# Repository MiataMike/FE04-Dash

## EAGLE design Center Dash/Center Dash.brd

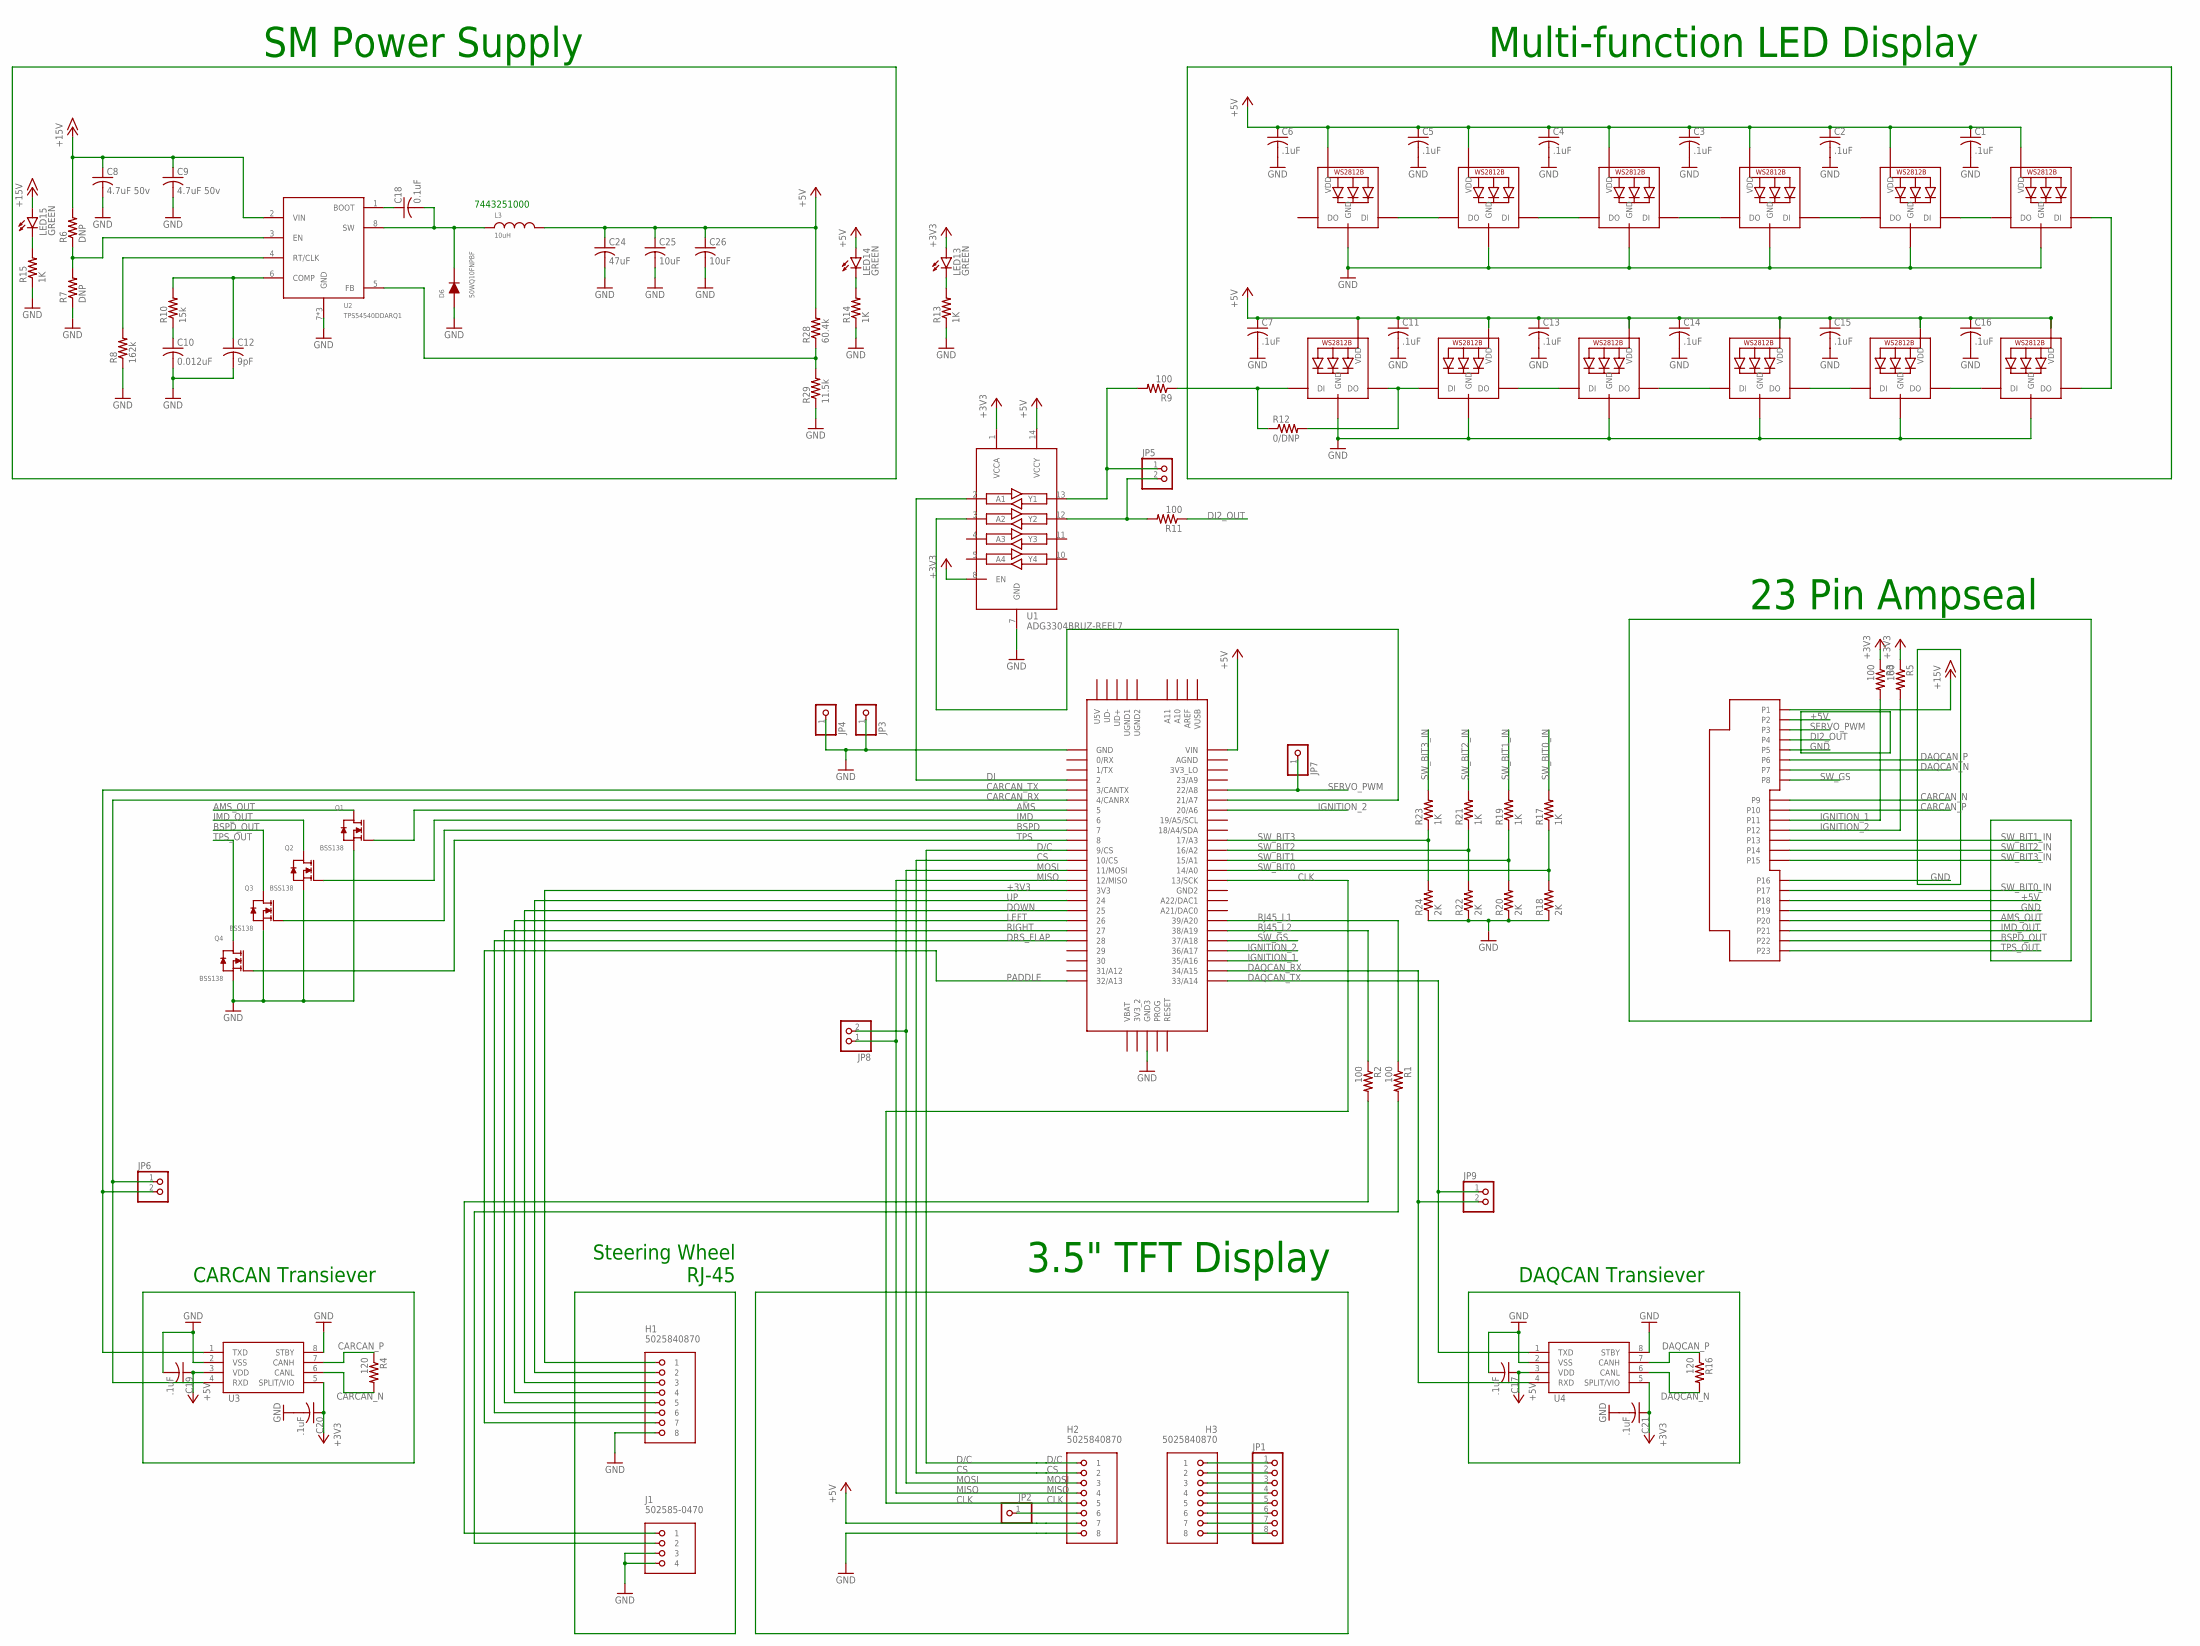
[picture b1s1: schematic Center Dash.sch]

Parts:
C1, C2, C3, C4, C5, C6, C7, C11, C13, C14, C15, C16: .1uF; C0603K; PARTNO GRM188R61A106KE69D
C8, C9: 4.7uF 50v; C1206; PARTNO GRM31CR71H475KA12L
C10: 0.012uF; C0603K; PARTNO GRM188R71H123KA01D
C12: 9pF; C0603K; PARTNO GRM1885C1H9R0DA01D
C17, C19, C20, C21: .1uF; C0805
C18: 0.1uF; C0603K; PARTNO GRM188R71E104KA01D
C24: 47uF; C1206; PARTNO GRM31CR61A476ME15L
C25, C26: 10uF; C0603K; PARTNO GRM188R61A106KE69D
D6: 50WQ10FNPBF; DPAK; PARTNO VS-50WQ10FNPBF
H1, H2, H3: 5025840870; MOLEX-CLIKMATE-8-VERTICAL-HEADER
J1: 502585-0470; MOLEX-CLIKMATE-4-R/A
JP1: PINHD-1X8; 1X08
JP2, JP3, JP4, JP7: PINHD-1X1; 1X01
JP5, JP6, JP8, JP9: PINHD-1X2; 1X02
L3: 10uH; WURTH-744325XXXX; PARTNO 7443251000
LED1, LED2, LED3, LED4, LED5, LED6, LED7, LED8, LED9, LED10, LED11, LED12: WS2812B5050; WS2812B
LED13, LED14, LED15: GREEN; CHIP-LED0805; PARTNO 598-8170-107F
Q1, Q2, Q3, Q4: BSS138
R1, R2, R3, R5, R9, R11: 100; R0805
R4, R16: 120; R0805
R6, R7: DNP; R0603; PARTNO *
R8: 162k; R0603; PARTNO ERJ-3EKF1623V
R10: 15k; R0603; PARTNO ERJ-3EKF1502V
R12: 0/DNP; R0805
R13, R14, R15, R17, R19, R21, R23: 1K; R0805; PARTNO ERJ-6ENF1001V
R18, R20, R22, R24: 2K; R0805; PARTNO ERJ-6ENF1001V
R28: 60.4k; R0603; PARTNO ERJ-3EKF6042V
R29: 11.5k; R0603; PARTNO ERJ-3EKF1152V
U1: ADG3304BRUZ-REEL7; ADG3304
U2: TPS54540DDARQ1; TPS54540; PARTNO TPS54540DDAR
U3, U4: MCP256X-SOIC; SOIC8-N_MC
U$1: TE-776200-1
U$2: TEENSY_3.5/3.6

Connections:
5VREG_EN: R6.1, R7.2, U2.3 (EN)
+3V3: C20.1, C21.1, H1.1, LED13.A, R3.1, R5.1, U1.1 (VCCA), U1.8 (EN), U3.5 (SPLIT/VIO), U4.5 (SPLIT/VIO), U$2.3V3
+5V: C1.1, C2.1, C3.1, C4.1, C5.1, C6.1, C7.1, C11.1, C13.1, C14.1, C15.1, C16.1, C17.1, C19.1, C24.1, C25.1, C26.1, H2.7, L3.P$2, LED1.1-VDD (VDD), LED2.1-VDD (VDD), LED3.1-VDD (VDD), LED4.1-VDD (VDD), LED5.1-VDD (VDD), LED6.1-VDD (VDD), LED7.1-VDD (VDD), LED8.1-VDD (VDD), LED9.1-VDD (VDD), LED10.1-VDD (VDD), LED11.1-VDD (VDD), LED12.1-VDD (VDD), LED14.A, R28.2, U1.14 (VCCY), U3.3 (VDD), U4.3 (VDD), U$1.P$2 (P2), U$1.P$18 (P18), U$2.VIN
+15V: C8.1, C9.1, LED15.A, R6.2, U2.2 (VIN), U$1.P$1 (P1)
AMS: Q1.G, U$2.5
AMS_OUT: Q1.D, U$1.P$20 (P20)
BOOT_5V: C18.1, U2.1 (BOOT)
BSPD: Q3.G, U$2.7
BSPD_OUT: Q3.D, U$1.P$22 (P22)
CARCAN_N: R4.2, U3.6 (CANL), U$1.P$9 (P9)
CARCAN_P: R4.1, U3.7 (CANH), U$1.P$10 (P10)
CARCAN_RX: JP6.1, U3.4 (RXD), U$2.4/CANRX
CARCAN_TX: JP6.2, U3.1 (TXD), U$2.3/CANTX
CLK: H2.5, U$2.13/SCK
COMP_5V: C12.1, R10.2, U2.6 (COMP)
CS: H2.2, U$2.10/CS
D/C: H2.1, U$2.9/CS
DAQCAN_N: R16.2, U4.6 (CANL), U$1.P$7 (P7)
DAQCAN_P: R16.1, U4.7 (CANH), U$1.P$6 (P6)
DAQCAN_RX: JP9.2, U4.4 (RXD), U$2.34/A15
DAQCAN_TX: JP9.1, U4.1 (TXD), U$2.33/A14
DI: U1.2 (A1), U$2.2
DI2_MORE: JP5.2, R11.2, U1.12 (Y2)
DI2_OUT: R11.1, U$1.P$4 (P4)
DI_MORE: U1.3 (A2), U$2.21/A7
DOWN: H1.3, U$2.25
DRS_FLAP: H1.6, U$2.28
FB_5V: R28.1, R29.2, U2.5 (FB)
GND: C1.2, C2.2, C3.2, C4.2, C5.2, C6.2, C7.2, C8.2, C9.2, C10.2, C11.2, C12.2, C13.2, C14.2, C15.2, C16.2, C17.2, C19.2, C20.2, C21.2, C24.2, C25.2, C26.2, D6.1 (ANODE), D6.3 (ANODE), H1.8, H2.8, J1.3, J1.4, JP3.1, JP4.1, LED1.3-GND (GND), LED2.3-GND (GND), LED3.3-GND (GND), LED4.3-GND (GND), LED5.3-GND (GND), LED6.3-GND (GND), LED7.3-GND (GND), LED8.3-GND (GND), LED9.3-GND (GND), LED10.3-GND (GND), LED11.3-GND (GND), LED12.3-GND (GND), Q1.S, Q2.S, Q3.S, Q4.S, R7.1, R8.1, R13.1, R14.1, R15.1, R18.1, R20.1, R22.1, R24.1, R29.1, U1.7 (GND), U2.7 (GND), U2.PAD (GND), U2.PAD1 (GND), U3.2 (VSS), U3.8 (STBY), U4.2 (VSS), U4.8 (STBY), U$1.P$5 (P5), U$1.P$16 (P16), U$1.P$19 (P19), U$2.GND, U$2.GND3
IGNITION_1: R3.2, U$1.P$11 (P11), U$2.35/A16
IGNITION_2: R5.2, U$1.P$12 (P12), U$2.20/A6, U$2.36/A17
IMD: Q2.G, U$2.6
IMD_OUT: Q2.D, U$1.P$21 (P21)
LEFT: H1.4, U$2.26
MISO: H2.4, JP8.1, U$2.12/MISO
MOSI: H2.3, JP8.2, U$2.11/MOSI
unnamed: LED1.2-DOUT (DO), LED2.4-DIN (DI), R12.2
unnamed: H3.1, JP1.1
unnamed: LED2.2-DOUT (DO), LED3.4-DIN (DI)
unnamed: LED3.2-DOUT (DO), LED4.4-DIN (DI)
unnamed: LED4.2-DOUT (DO), LED5.4-DIN (DI)
unnamed: LED5.2-DOUT (DO), LED6.4-DIN (DI)
unnamed: LED6.2-DOUT (DO), LED7.4-DIN (DI)
unnamed: LED1.4-DIN (DI), R9.1, R12.1
unnamed: H3.2, JP1.2
unnamed: H3.3, JP1.3
unnamed: H3.4, JP1.4
unnamed: H3.5, JP1.5
unnamed: H3.6, JP1.6
unnamed: H3.7, JP1.7
unnamed: LED14.C, R14.2
unnamed: JP5.1, R9.2, U1.13 (Y1)
unnamed: LED15.C, R15.2
unnamed: H3.8, JP1.8
unnamed: H2.6, JP2.1
unnamed: C10.1, R10.1
unnamed: J1.1, R2.2
unnamed: J1.2, R1.2
unnamed: LED7.2-DOUT (DO), LED8.4-DIN (DI)
unnamed: LED8.2-DOUT (DO), LED9.4-DIN (DI)
unnamed: LED9.2-DOUT (DO), LED10.4-DIN (DI)
unnamed: LED10.2-DOUT (DO), LED11.4-DIN (DI)
unnamed: LED11.2-DOUT (DO), LED12.4-DIN (DI)
unnamed: LED13.C, R13.2
PADDLE: H1.7, U$2.32/A13
RIGHT: H1.5, U$2.27
RJ45_L1: R1.1, U$2.39/A20
RJ45_L2: R2.1, U$2.38/A19
RT_5V: R8.2, U2.4 (RT/CLK)
SERVO_PWM: JP7.1, U$1.P$3 (P3), U$2.22/A8
SW_5V: C18.2, D6.2 (CATHODE), L3.P$1, U2.8 (SW)
SW_BIT0: R17.1, R18.2, U$2.14/A0
SW_BIT0_IN: R17.2, U$1.P$17 (P17)
SW_BIT1: R19.1, R20.2, U$2.15/A1
SW_BIT1_IN: R19.2, U$1.P$13 (P13)
SW_BIT2: R21.1, R22.2, U$2.16/A2
SW_BIT2_IN: R21.2, U$1.P$14 (P14)
SW_BIT3: R23.1, R24.2, U$2.17/A3
SW_BIT3_IN: R23.2, U$1.P$15 (P15)
SW_GS: U$1.P$8 (P8), U$2.37/A18
TPS: Q4.G, U$2.8
TPS_OUT: Q4.D, U$1.P$23 (P23)
UP: H1.2, U$2.24

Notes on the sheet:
7443251000
Steering Wheel RJ-45
Multi-function LED Display
3.5" TFT Display
23 Pin Ampseal
SM Power Supply
CARCAN Transiever
DAQCAN Transiever

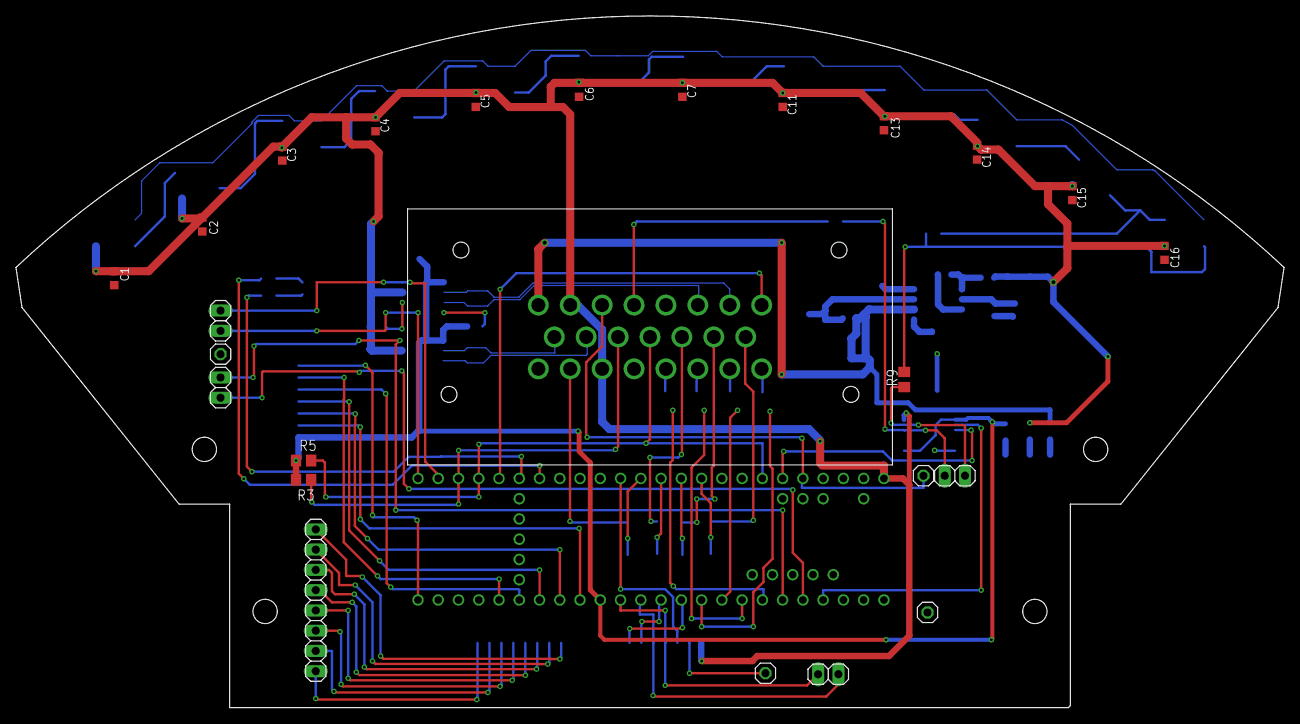
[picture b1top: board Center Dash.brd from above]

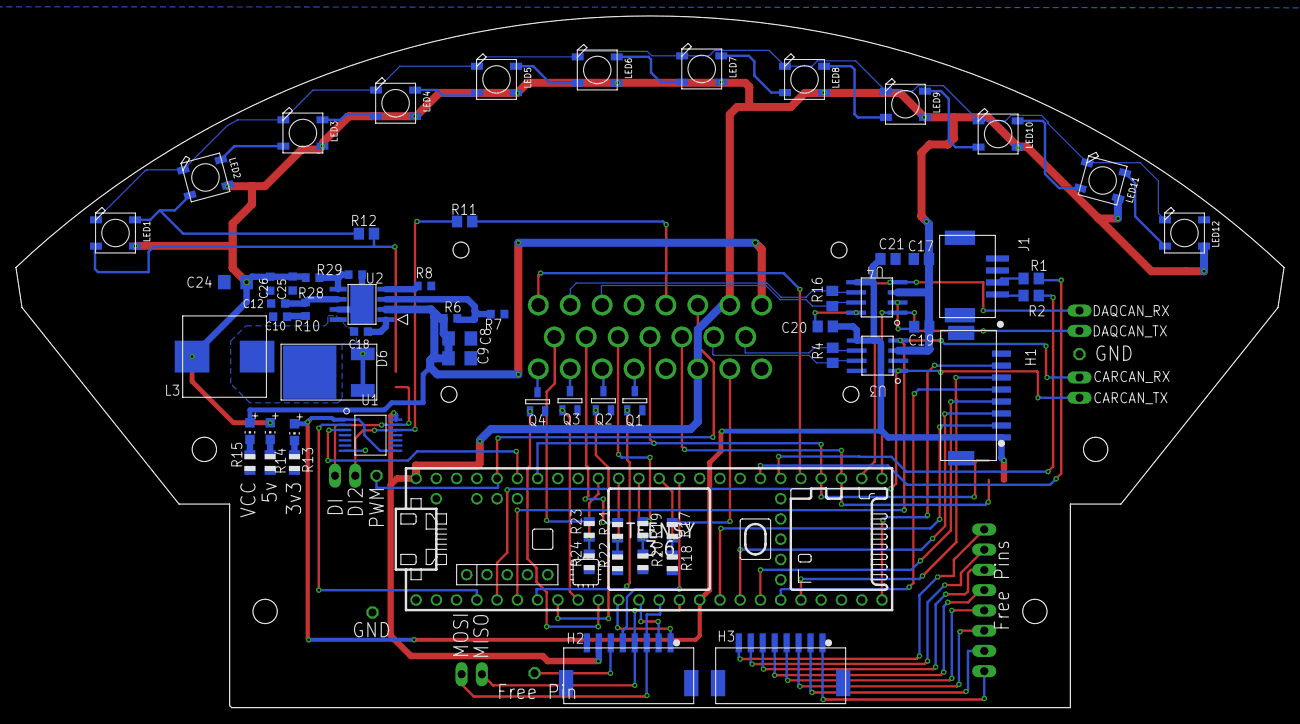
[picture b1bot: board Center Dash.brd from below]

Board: 2 copper layers, 159.0 x 86.7 mm, 90 parts (65 on the bottom side), 83 nets.

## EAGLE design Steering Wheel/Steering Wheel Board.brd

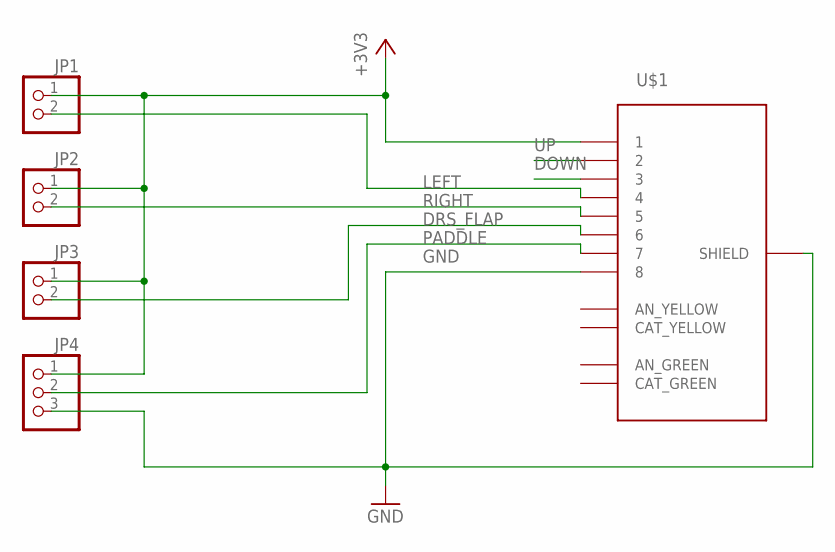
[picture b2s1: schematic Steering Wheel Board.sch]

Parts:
JP1, JP2, JP3: PINHD-1X2; 1X02
JP4: PINHD-1X3; 1X03
U$1: RJ-45_12-PIN; RJ-45

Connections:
+3V3: JP1.1, JP2.1, JP3.1, JP4.1, U$1.P$1 (1)
DOWN: U$1.P$3 (3)
DRS_FLAP: JP3.2, U$1.P$6 (6)
GND: JP4.3, U$1.P$8 (8), U$1.P$13 (SHIELD)
LEFT: JP1.2, U$1.P$4 (4)
PADDLE: JP4.2, U$1.P$7 (7)
RIGHT: JP2.2, U$1.P$5 (5)
UP: U$1.P$2 (2)

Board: 2 copper layers, 5 parts (0 on the bottom side), 6 nets, no tracks yet.

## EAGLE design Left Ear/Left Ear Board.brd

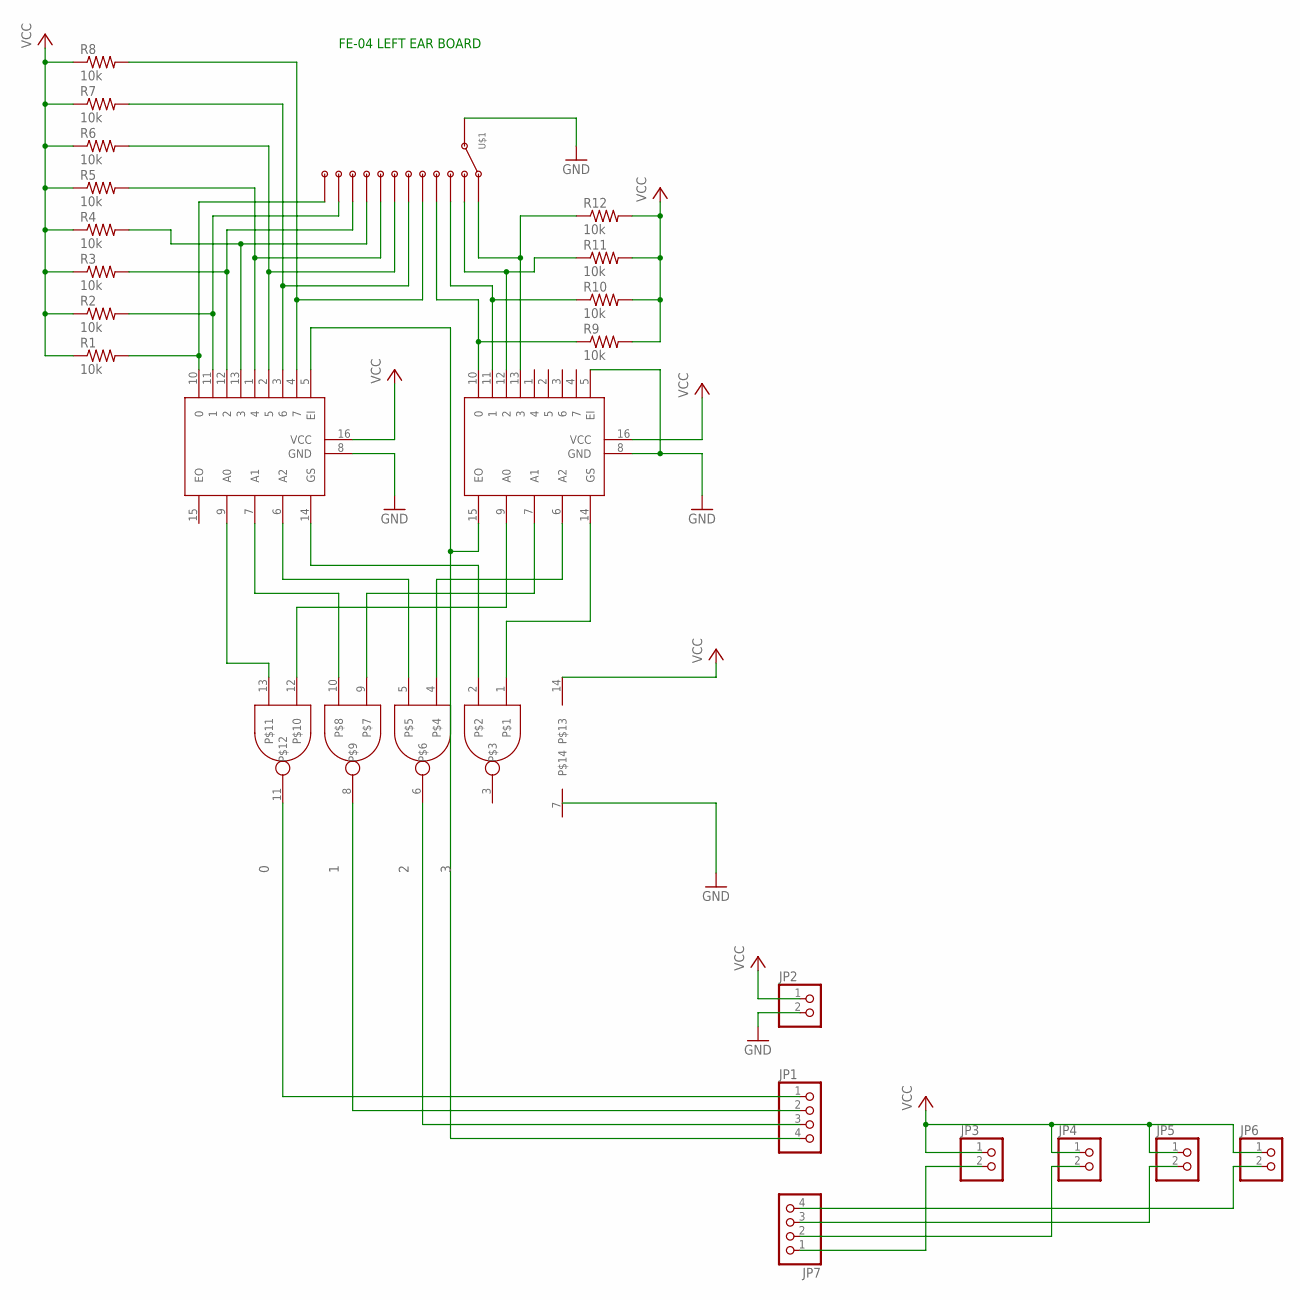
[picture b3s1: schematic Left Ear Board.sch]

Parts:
JP1, JP7: PINHD-1X4; 1X04
JP2, JP3, JP4, JP5, JP6: PINHD-1X2; 1X02
R1, R2, R3, R4, R5, R6, R7, R8, R9, R10, R11, R12: 10k; R0603; PARTNO ERJ-3EKF2201V
U$1: 12-POSITION-ROTARY; MC00L1NCQF
U$2, U$3: SN74LS148D; SOIC-16
U$4: QUAD_NAND; SOIC-14

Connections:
0: JP1.1, U$4.11
1: JP1.2, U$4.8
2: JP1.3, U$4.6
3: JP1.4, U$2.5 (EI), U$3.15 (EO)
GND: JP2.2, U$1.P$13 (WIPER), U$2.8 (GND), U$3.5 (EI), U$3.8 (GND)
unnamed: R1.2, U$1.P$12 (PIN12), U$2.10 (0)
unnamed: U$2.9 (A0), U$4.13
unnamed: U$3.9 (A0), U$4.12
unnamed: U$2.7 (A1), U$4.10
unnamed: U$3.7 (A1), U$4.9
unnamed: U$2.6 (A2), U$4.5
unnamed: U$3.6 (A2), U$4.4
unnamed: U$2.14 (GS), U$4.2
unnamed: U$3.14 (GS), U$4.1
unnamed: R9.1, U$1.P$4 (PIN4), U$3.10 (0)
unnamed: R10.1, U$1.P$3 (PIN3), U$3.11 (1)
unnamed: R11.1, U$1.P$2 (PIN2), U$3.12 (2)
unnamed: R12.1, U$1.P$1 (PIN1), U$3.13 (3)
unnamed: R2.2, U$1.P$11 (PIN11), U$2.11 (1)
unnamed: R3.2, U$1.P$10 (PIN10), U$2.12 (2)
unnamed: R4.2, U$1.P$9 (PIN9), U$2.13 (3)
unnamed: R5.2, U$1.P$8 (PIN8), U$2.1 (4)
unnamed: R6.2, U$1.P$7 (PIN7), U$2.2 (5)
unnamed: R7.2, U$1.P$6 (PIN6), U$2.3 (6)
unnamed: R8.2, U$1.P$5 (PIN5), U$2.4 (7)
unnamed: JP3.2, JP7.1
unnamed: JP4.2, JP7.2
unnamed: JP5.2, JP7.3
unnamed: JP6.2, JP7.4
VCC: JP2.1, JP3.1, JP4.1, JP5.1, JP6.1, R1.1, R2.1, R3.1, R4.1, R5.1, R6.1, R7.1, R8.1, R9.2, R10.2, R11.2, R12.2, U$2.16 (VCC), U$3.16 (VCC), U$4.14

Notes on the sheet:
FE-04 LEFT EAR BOARD

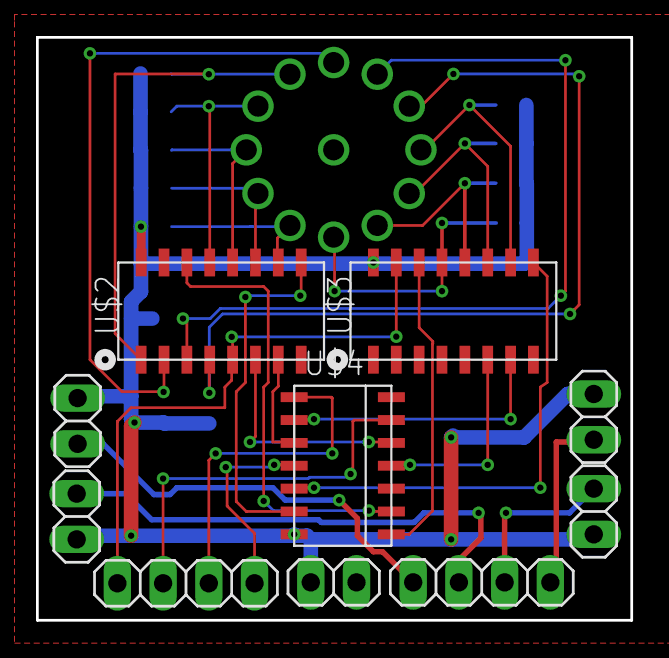
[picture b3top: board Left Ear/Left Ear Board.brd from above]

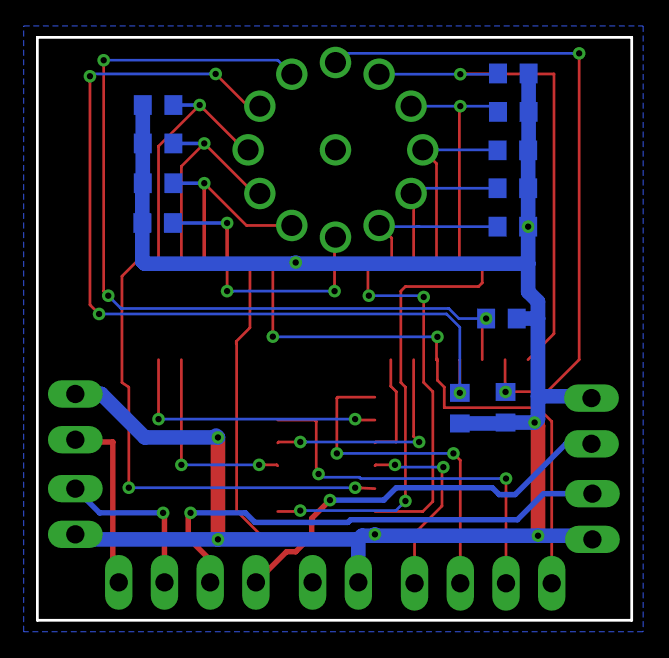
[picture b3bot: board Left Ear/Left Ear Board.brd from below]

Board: 2 copper layers, 33.0 x 32.4 mm, 23 parts (12 on the bottom side), 30 nets.

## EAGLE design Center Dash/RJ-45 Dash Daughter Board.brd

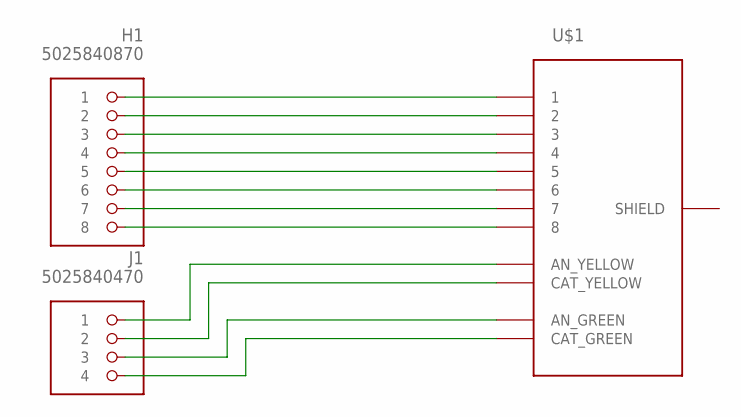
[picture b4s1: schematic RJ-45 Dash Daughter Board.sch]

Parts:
H1: 5025840870; MOLEX-CLIKMATE-8-VERTICAL-HEADER
J1: 5025840470; MOLEX-CLIKMATE-4-VERTICAL-HEADER
U$1: RJ-45_12-PIN; RJ-45

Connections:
unnamed: H1.1, U$1.P$1 (1)
unnamed: H1.2, U$1.P$2 (2)
unnamed: H1.3, U$1.P$3 (3)
unnamed: H1.4, U$1.P$4 (4)
unnamed: H1.5, U$1.P$5 (5)
unnamed: H1.6, U$1.P$6 (6)
unnamed: H1.7, U$1.P$7 (7)
unnamed: H1.8, U$1.P$8 (8)
unnamed: J1.1, U$1.P$9 (AN_YELLOW)
unnamed: J1.2, U$1.P$10 (CAT_YELLOW)
unnamed: J1.3, U$1.P$11 (AN_GREEN)
unnamed: J1.4, U$1.P$12 (CAT_GREEN)

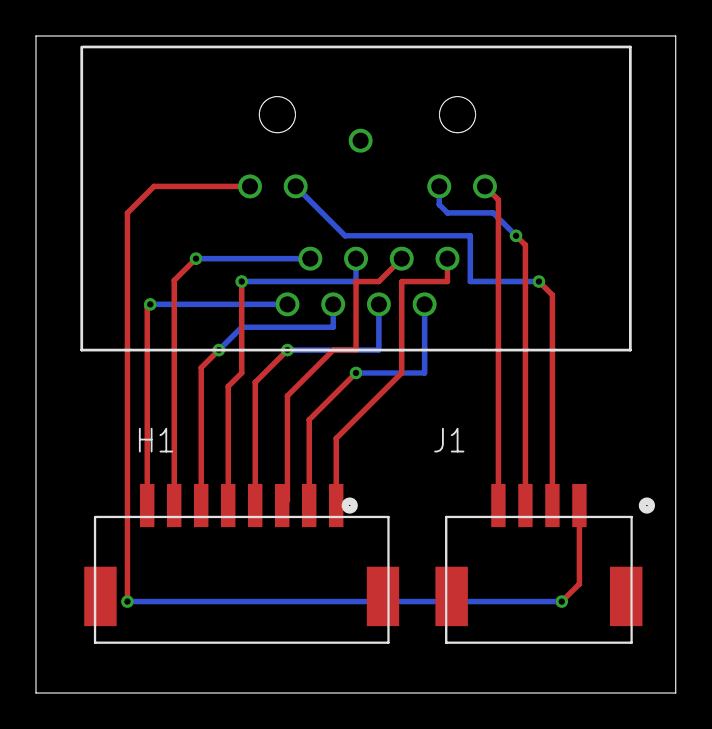
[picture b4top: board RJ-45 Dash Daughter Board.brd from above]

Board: 2 copper layers, 35.5 x 36.5 mm, 3 parts (0 on the bottom side), 12 nets.

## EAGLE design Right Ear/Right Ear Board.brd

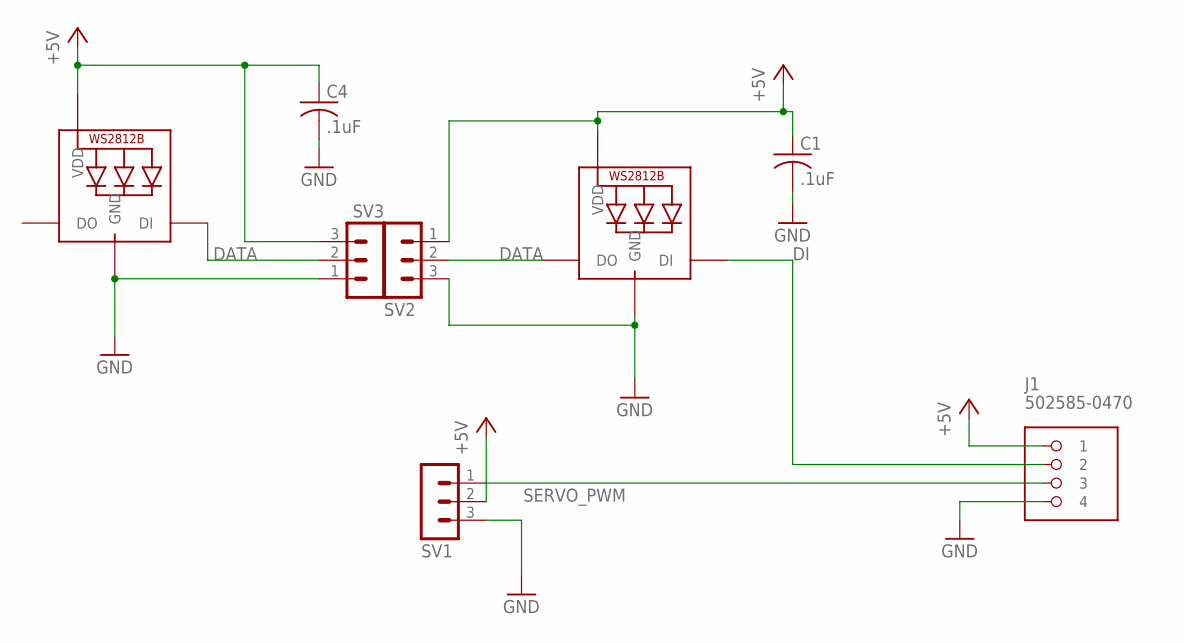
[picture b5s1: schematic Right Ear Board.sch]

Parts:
C1, C4: .1uF; C0603K; PARTNO GRM188R61A106KE69D
J1: 502585-0470; MOLEX-CLIKMATE-4-R/A
LED1, LED7: WS2812B5050; WS2812B
SV1, SV2, SV3: MA03-1

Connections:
+5V: C1.1, C4.1, J1.1, LED1.1-VDD (VDD), LED7.1-VDD (VDD), SV1.2, SV2.1, SV3.3
DATA: LED1.2-DOUT (DO), LED7.4-DIN (DI), SV2.2, SV3.2
DI: J1.2, LED1.4-DIN (DI)
GND: C1.2, C4.2, J1.4, LED1.3-GND (GND), LED7.3-GND (GND), SV1.3, SV2.3, SV3.1
SERVO_PWM: J1.3, SV1.1

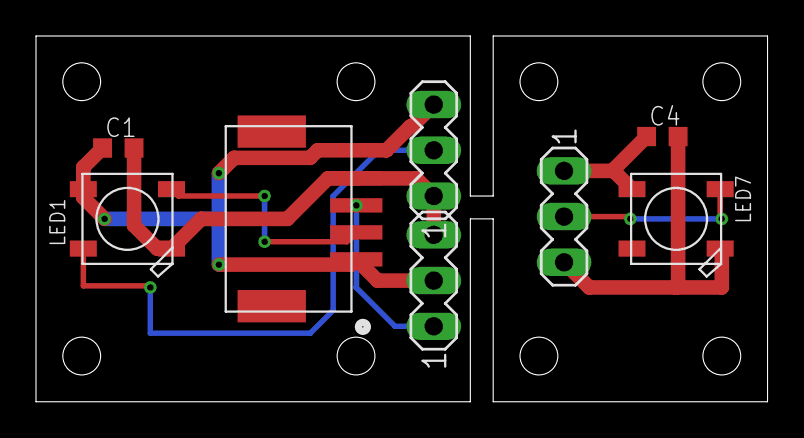
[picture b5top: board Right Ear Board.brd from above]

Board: 2 copper layers, 40.6 x 20.3 mm, 8 parts (0 on the bottom side), 5 nets.

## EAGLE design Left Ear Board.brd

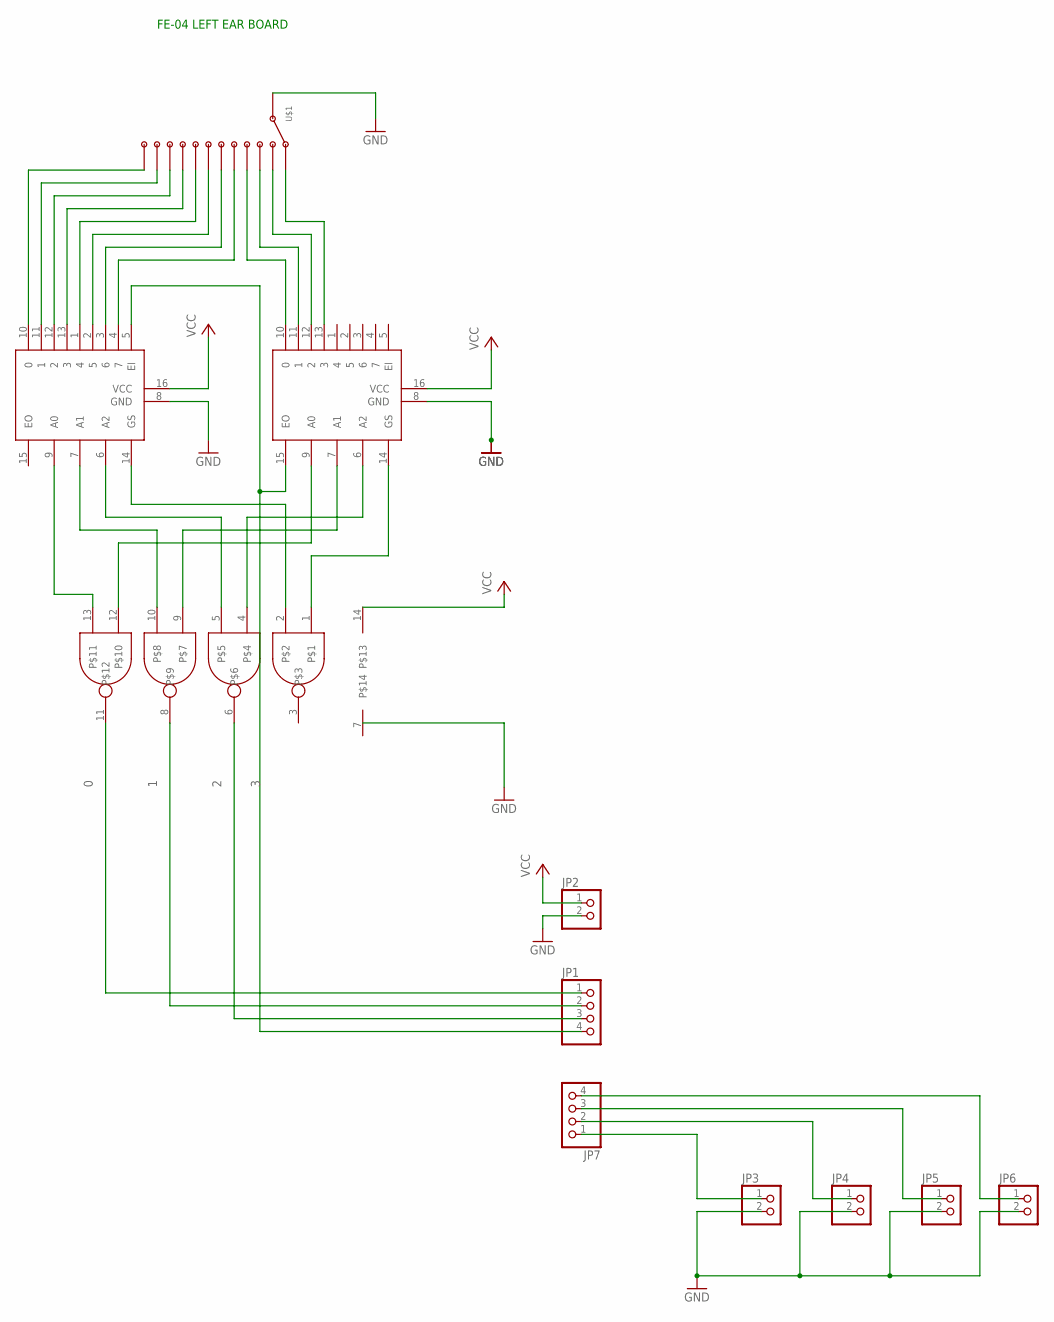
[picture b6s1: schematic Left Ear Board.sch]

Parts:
JP1, JP7: PINHD-1X4; 1X04
JP2, JP3, JP4, JP5, JP6: PINHD-1X2; 1X02
U$1: 12-POSITION-ROTARY; MC00L1NCQF
U$2, U$3: SN74LS148D; SOIC-16
U$4: QUAD_NAND; SOIC-14

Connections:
0: JP1.1, U$4.11
1: JP1.2, U$4.8
2: JP1.3, U$4.6
3: JP1.4, U$2.5 (EI), U$3.15 (EO)
GND: JP2.2, JP3.2, JP4.2, JP5.2, JP6.2, U$1.P$13 (WIPER), U$2.8 (GND), U$3.8 (GND)
unnamed: U$1.P$12 (PIN12), U$2.10 (0)
unnamed: U$2.9 (A0), U$4.13
unnamed: U$3.9 (A0), U$4.12
unnamed: U$2.7 (A1), U$4.10
unnamed: U$3.7 (A1), U$4.9
unnamed: U$2.6 (A2), U$4.5
unnamed: U$3.6 (A2), U$4.4
unnamed: U$2.14 (GS), U$4.2
unnamed: U$3.14 (GS), U$4.1
unnamed: U$1.P$4 (PIN4), U$3.10 (0)
unnamed: U$1.P$3 (PIN3), U$3.11 (1)
unnamed: U$1.P$2 (PIN2), U$3.12 (2)
unnamed: U$1.P$1 (PIN1), U$3.13 (3)
unnamed: U$1.P$11 (PIN11), U$2.11 (1)
unnamed: U$1.P$10 (PIN10), U$2.12 (2)
unnamed: U$1.P$9 (PIN9), U$2.13 (3)
unnamed: U$1.P$8 (PIN8), U$2.1 (4)
unnamed: U$1.P$7 (PIN7), U$2.2 (5)
unnamed: U$1.P$6 (PIN6), U$2.3 (6)
unnamed: U$1.P$5 (PIN5), U$2.4 (7)
unnamed: JP3.1, JP7.1
unnamed: JP4.1, JP7.2
unnamed: JP5.1, JP7.3
unnamed: JP6.1, JP7.4
VCC: JP2.1, U$2.16 (VCC), U$3.16 (VCC), U$4.14

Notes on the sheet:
FE-04 LEFT EAR BOARD

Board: 2 copper layers, 11 parts (0 on the bottom side), 30 nets, no tracks yet.

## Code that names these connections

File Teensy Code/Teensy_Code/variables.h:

#ifndef VARIABLES_H
#define VARIABLES_H

#include <SPI.h>
#include <Adafruit_NeoPixel.h>
#include <Adafruit_NeoMatrix.h>
#include <Adafruit_GFX.h>
#include <HX8357_t3.h>
#include <FlexCAN_t3.h>
#include <kinetis_flexcan_t3.h>
#include <SD.h>
#include <string.h>
#include <Servo.h>

//Setting up Pins
#define CD_neo_pixel_DI 2 //Dash
#define NUM_CD_PIXELS 12

#define CARCAN_TX 3  //CAN0
#define CARCAN_RX 4

#define DAQCAN_TX 33  //CAN1
#define DAQCAN_RX 34
 
#define AMS_light 5 //Left ear
#define IMD_light 6
#define BSPD_light 7
#define QBAI_light 8

#define DC 9
#define CS 10
#define MOSI 11
#define MISO 12
#define CLK 13
#define SDCS BUILTIN_SDCARD

#define Paddle A13
#define up_button 24
#define down_button 25
#define left_button 26
#define right_button 27
#define DRS_flap 28

#define servo_PWM 22 //Right ear
#define RE_neo_pixel_DI 21
#define NUM_RE_PIXELS 2

#define RJ45_L1 20
#define RJ45_L2 19

#define Ignition_1 35
#define Ignition_2 20

#define SW_bit0 14
#define SW_bit1 15
#define SW_bit2 16
#define SW_bit3 17
#define GS_pin 37

#define ON true
#define OFF false

//0x20
extern uint16_t throttleOneRaw;
extern float throttleOneF;
extern uint16_t throttleTwoRaw;
extern float throttleTwoF;
extern uint16_t brakePressureFrontRaw;
extern float brakePressureFrontF;
extern uint16_t brakePressureRearRaw;
extern float brakePressureRearF;
extern bool brakePressureBool;
extern float brakeMax;
extern bool throttlePlaus;
extern float throttleDiff;

//0x28
extern bool BSPDfault; //statuses
extern bool IMDfault;
extern bool AMSfault;
extern bool TBPfault; //Throttle Brake Plausibility (QBAI)
extern bool driveActive;
extern bool previousdriveActive;
extern bool startActive;
extern bool shutdownActive;
extern uint8_t lvVoltage;
extern float lvVoltageF;
extern float previouslvVoltageF;
extern int16_t carSpeed; //car speed read through CAN bus
extern int16_t previouscarSpeed;
extern double carSpeedF; //float
extern uint8_t brakePosition;
extern uint8_t previousbrakePosition;

//0x29
extern uint16_t MCTemp;
extern float MCTempF;
extern uint16_t motorTemp;
extern float motorTempF;
extern uint16_t batteryTemp;
extern float batteryTempF;

//0x41
extern bool prechargeContactor;
extern bool negativeContactor;
extern bool positiveContactor;
extern uint16_t faulted;
extern uint16_t previousmaxCellTemp;
extern uint16_t maxCellTemp;
extern float maxCellTempF;
extern uint16_t minCellTemp;
extern float minCellTempF;
extern uint16_t previousHVSOC;
extern uint16_t HVSOC; //High Voltage State Of Charge
extern float HVSOCF; //float for gauges

//0x42
extern uint16_t packVoltage;
extern float packVoltageF;
extern uint16_t vehicleVoltage;
extern float vehicleVoltageF;
extern uint16_t maxCellVoltage;
extern float maxCellVoltageF;
extern uint16_t minCellVoltage;
extern float minCellVoltageF;

//0x43
extern uint16_t packCurrent;
extern float packCurrentF;

//Dash
extern uint8_t driveMode;
extern uint8_t previousdriveMode;
extern uint8_t dashpage;
extern uint8_t previousdashpage;
extern uint8_t dashcount;
extern String previousTitle;
extern uint8_t razzledelay;
extern bool temprangechange;
extern bool brakeScreen;
extern bool previouslybrakeScreen;
extern uint16_t maxTorque;
extern uint16_t previousmaxTorque;

//CAN Setup
extern FlexCAN CARCAN;
extern FlexCAN DAQCAN;
extern CAN_message_t txmsg,rxmsg;

//TFT Screen Setup
extern HX8357_t3 tft;
extern int16_t tft_width;
extern int16_t tft_height;
extern uint8_t rotation;

//Key
extern bool on;
extern bool previouslyon;
extern bool previouslyStartActive;

//NeoPixels
extern Adafruit_NeoPixel cdpixels;
extern Adafruit_NeoPixel repixels;

//State of Charge Servo
extern Servo socservo;
extern uint8_t servoval;

extern bool secretScreen;
extern bool previouslysecretScreen;

//debounce 
extern unsigned long Ldebounce; 
extern unsigned long Rdebounce; 
extern unsigned long DRSdebounce; 
 
//regen 
#define shortedThreshold 69420 
#define groundThreshold 0 
#define maxRegen 90 
extern uint8_t regen_scaled;

//DRS
extern bool DRSengaged;

//Fans
extern uint8_t highTemp;
extern uint8_t lowTemp;
extern float fanPWM;

extern const unsigned char STlogo [] PROGMEM;

#endif

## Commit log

2017-09-03 Added Teensy, Power Converter, and LED's
2017-09-04 Just a few thoughts
2017-09-04 added git ignore
2018-01-20 Changed Teensy from 3.1 to 3.5/6
2018-01-24 Worked on board schematic
2018-01-25 Finished Board Schematic. Routing needs to be done.
2018-01-25 Remove all the backups
2018-01-25 Finished board layout
2018-01-25 Worked on schematic. Connected some wires
2018-01-26 Added some connectors.
2018-01-26 Gave Mike an Analog Line
2018-01-26 Worked on connecor pin
2018-01-26 Finished Schematic?? Probably.
2018-01-26 Rough board work
2018-01-27 Finished Schematic
2018-01-27 Begin Board layout
2018-01-27 Needs to be looked over and modeled in solidworks
2018-01-27 Added 4 pin clickmate for rj45
2018-01-27 Added resistors for LEDs
2018-01-27 Created RJ-45 Device, and RJ-45 Dash Daughter Board
2018-01-27 Created Right Ear Board and made adjustments to Dash
2018-01-28 Made a folder for Teensy Code and downloaded libraries
2018-01-28 Defined Pins, Updated names on schematic
2018-02-07 Updated board layout
2018-02-08 Updated schematic and board layout
2018-02-08 Add in teensy libraries
2018-02-08 Remove the libraries??
2018-02-08 Add a note for how to get teensy libraries
2018-02-08 Finish board layout for main dash
2018-02-09 Updated Schematic
    *Warning* The board did not update with the schematic
2018-02-09 Brandon did a thing
2018-02-09 Fixed Ashers fuck up
2018-02-10 Update right ear boards
2018-02-10 Made changes
    Change LED caps to .1uF on right ear and center
    Add resistor to D2
    Add level shifters (1 for D1, 1 for D2)
    Add mount holes on right ear
2018-02-10 Made changes
    Change LED caps to .1uF on right ear and center
    Add resistor to D2
    Add level shifters (1 for D1, 1 for D2)
    Add mount holes on right ear
    Add mosfet for servo (see things to consider.txt)
2018-02-10 Redid right ear board layouts
2018-02-11 Added level shifter to center dash
2018-02-11 Done with board layouts
2018-02-13 Worked on code
    Updated board layouts since shit changed
2018-02-14 Added a little bit of code
2018-02-20 Started working on display
2018-02-28 Fix for daqbus CAN
    Added another can transceiver for the daq bus
    Moved the ignition1 and 2 to different pins to account for the teensy can bus lines
    Fixed the can code from flexcan
2018-02-28 Had to change a name from CARCAN to DAQCAN
2018-02-28 Update code for new CAN
2018-02-28 Add voltage dividers to 5V input lines
    Now we can use Teensy 3.6
2018-03-01 last minute fix again
2018-03-08 Change some code stuff
2018-03-10 Code shit
2018-03-10 Add libraries
2018-03-10 Add the logo that needs to be put in SD card
2018-03-13 Added more code stuffs
2018-03-13 added a common background
2018-03-13 Code stuff
2018-03-13 More code stuff
2018-03-13 More more code stuff
2018-03-14 More more more code stuff
2018-03-15 More more more more code stuff
2018-03-20 Fixed?? amp seal connector
2018-03-20 Rotate LEDs. Might fit better??
2018-03-20 Fix silk screens
2018-03-21 Stuff of the code variety
2018-03-22 Update schematic to remove last spare
2018-03-23 Made the servo do a thing
2018-03-23 Pixels only happen when ignition not on or razzle mode now
2018-03-24 I dont remember
2018-03-24 Fault light changes
2018-03-24 Add comments for enabling drive mode
2018-03-24 Added Neopixel Color guide and Servo needle
2018-03-24 here you go
2018-03-24 Updated Neopixel Battery Color Guide
2018-03-24 Added PNG
2018-03-24 life is happening
2018-03-25 CAN works now
2018-03-25 Upload Better can library
2018-03-25 Remove libraries.zip
2018-03-25 screen library
2018-03-25 Neomatrix library
2018-03-25 Optimized Code
2018-03-25 We did the things
2018-03-25 Needs testing. See description for changes
    Add logic for enabling drive mode
    Add logic for changing dashpage
    Updated the CAN receive functions
    Add logic for drive enabled light on right ear
    Add code for sending CAN message
2018-03-25 Fixes from testing
2018-03-25 Able to enable drive mode
2018-03-25 Add in Qbai light logic
2018-03-25 Add in page changing logic
2018-03-25 Put dash part files and stickers in
2018-03-25 bwah bwah it dont work perfectly
2018-03-25 I fucking hate wires. They are stupid and antennas are gay
2018-03-25 Lots of googliness happened here
2018-04-06 Added Steering Wheel Enclosure and Board
    Enclosure still needs RJ-45 jack and board taken into account. Board needs to be laid out.
2018-04-06 Someone flipped the ignition wires
2018-04-07 Remove the Bots fault
2018-04-08 Add mushroom mode
2018-05-03 stuff is dcone
2018-05-03 Fix drive Mode can message of destiny
2018-05-03 Mushroom to 9
2018-05-04 Fix dash temp lights
2018-05-09 Shit
2018-05-09 Fix driveMode numbers
2018-05-10 Reverse Mode
2018-05-11 Add speed
2018-05-11 magic
2018-05-11 hmmm what did i do???
2018-05-11 Add brake position
2018-05-11 Add special brake message for starting
2018-05-11 Add more brake message logic
2018-05-11 More stuff
2018-05-11 Add message for HV off
2018-05-11 Add images
2018-05-11 Secret Mode
2018-05-11 Thing
2018-05-11 dash page stuff
2018-05-11 Increase resolution of LV
2018-05-11 Stuff
2018-05-16 added regen code
2018-05-23 Fixes for regen
2018-05-23 Cooling Board stuff
2018-06-13 dash stickers
2018-06-13 updated regen algorithm
2019-03-12 Changed CAR CAN Output to match MasterBlaster
    Still need to remove excess drive modes. CAN message matches the spreadsheet.
2019-03-13 Removed unnecessary drive modes.
    RIP doggo and mushroom modes (for now). Should all hopefully work.
2019-03-14 Fixed some logic errors
    I was dumb when I removed the unnecessary drive modes.
2019-03-15 More Fixes
2019-03-15 Updated other file
2019-03-15 Small Changes
2019-03-16 Fixed small compilation errors.
2019-03-21 Added 10ms CAN update rate
2019-03-21 Cleaning things up
2019-04-19 Debugging for masterblaster
2019-04-23 WTF Asher
2019-05-04 Started fixing this awful code
2019-05-04 Bug fixes
2020-02-29 Fixing screen bugs
    fix fix fix fix
    added color scaling for SOC
    changed where borders are
    made things centered and prettyyy
    moved current drive mode to bottom
    when in cal mode you KNOW IT
2020-02-29 Revert "Fixing screen bugs"
    This reverts commit 6ac06dbf13a5eba1d1bc4c3b82cb937deedb7274.
2020-02-29 more changes
    i am sorry
2020-02-29 updates & bug fixes
    fixing bugs
2021-10-13 Fixed Ignition 2
2021-10-16 Fixed two of the via overlaps
2022-04-25 Create Teensy code compliation.pptx
    I had to clean install teensyduino on my laptop so I followed these instructions and was able to compile for t3.6
